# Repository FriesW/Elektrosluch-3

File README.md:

# Elektrosluch-3-Mini
A very small edition of the [Elektrosluch-3](https://github.com/LOM-instruments/Elektrosluch-3) by [LOM Instruments](https://lom.audio/).

## What it is
The Elektrosluch is an open-source device for listening to electromagnetic fields. Two inductors or coils of wire act as antennas to couple with stray magnetic fields. This particular model also functions as a general purpose audio amplifier. All functions are in stereo. Line output and external input are 3.5 mm (1/8") stereo jacks. The device is powered from a 9V battery.

Jonas Gruska of LOM Instruments, the original creator, has made an album using a device with the same circuit. It can be [listened to on Bandcamp](http://zvukolom.bandcamp.com/album/sensing-electromagnetics) and is representative of what you can hear with this device.

## Reason for Creation
1. I find it a fun game to make PCBs as small as possible.
2. The original project lacked a BOM.
3. The original project was made in Eagle. I prefer KiCad.
4. I wanted to use the Elektrosluch as a gift for my brother.

## BOM and Part Selection
Audio capacitors and potentiometer were selected as recommended from the original LOM project. These are the bulkiest portion, and a future development could be replacing these with much smaller equivalences. Everything else was selected to be surface mount and as small as possible. Custom KiCad footprints had to be made for many of the parts. The BOM lists standard inductors for the "antennas," but handwound wire might produce more desirable results, as the inductors will be engineered to reduce coupling as much as possible.

## Assembly
Some projects say "advanced soldering skills required," and you might scoff at it. However, this is not one to scoff at. Small SMD parts are used and spaced very closely together. It is necessary to plan many steps ahead, such that you have enough room to place every component.

## PCBs
The PCB is also [shared through OSH Park](https://oshpark.com/shared_projects/8xzPLFLW) and can be directly ordered from there. You'll get three boards for $8.75. ~However, I might have a few lying around, so if you are going to build one, PM me and I'll look to see if I have extras.~ All gone! Still feel free to PM me if you have any questions.

## Modifications
If you want to further develop the project, [KiCad](http://kicad-pcb.org/) can be obtained for free, as in free speech. The KiCad project files use custom schematic symbols and footprints which are in my [personal KiCad library](https://github.com/FriesW/KiCad-Library).

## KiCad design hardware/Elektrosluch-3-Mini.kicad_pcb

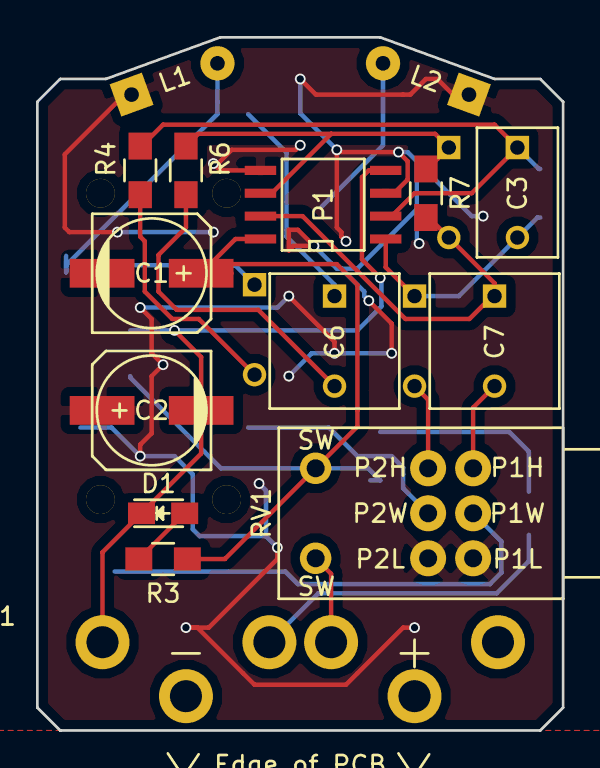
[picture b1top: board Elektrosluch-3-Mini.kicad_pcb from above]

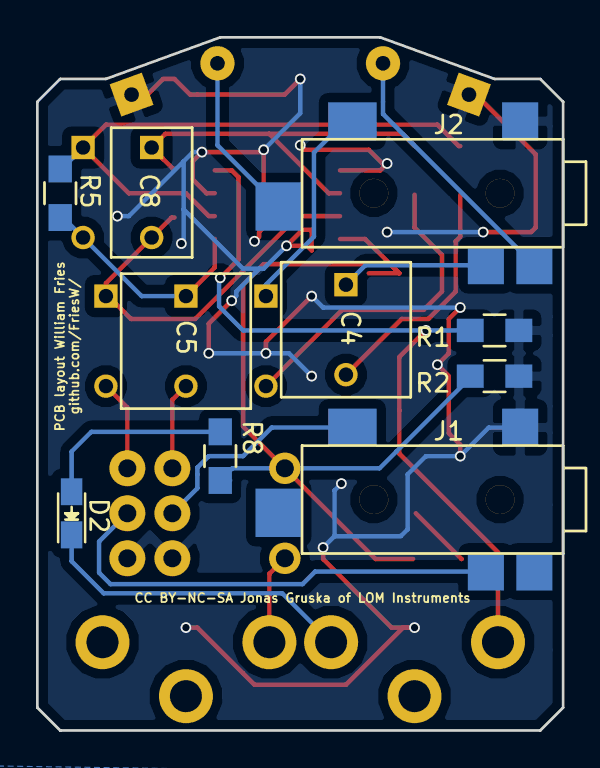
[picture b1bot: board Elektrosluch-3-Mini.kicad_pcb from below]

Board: 2 copper layers, 29.2 x 38.5 mm, 25 parts (10 on the bottom side), 20 nets.

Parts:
BT1: 9V; 9V_Battery_Snaps
C1, C2: 220uF; c_elec_6.3x7.7
C3, C8: 47pF; C_Rect_L7.2_W4.5_P5
C4, C5, C6, C7: 2.2uF; C_Rect_L7.2_W7.2_P5
D1, D2: LED; LED-0805-HandSoldering
J1, J2: JACK_TRS_5PINS; Switchcraft_TRS_Jack_SMD
L1, L2: 22mH; INDUCTOR_V_WO_CIRCLE
P1: DIL8; SOIC-8-N-HandSoldering
R1, R2: 100k; R_0805_HandSoldering
R3, R4, R6, R8: 1k; R_0805_HandSoldering
R5, R7: 390k; R_0805_HandSoldering
RV1: DUAL_SWITCHED_POT; Dual_Switched_Pot

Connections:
+5V: C1.1, P1.8, R1.1, R3.1, R8.1, RV1.7
-5V: BT1.2, C2.2, D1.1, D2.1, P1.4, R2.2
/AO1: C3.2, C5.1, P1.1, R5.2
/AO2: C7.1, C8.2, P1.7, R7.2
/CH1: C3.1, P1.2, R4.2, R5.1
/CH2: C8.1, P1.6, R6.2, R7.1
GND: C1.2, C2.1, J1.1, J2.1, L1.1, L2.1, P1.3, P1.5, R1.2, R2.1, RV1.3, RV1.6
unnamed: BT1.1, RV1.8
unnamed: C4.1, J2.3
unnamed: C4.2, R4.1
unnamed: C5.2, RV1.4
unnamed: C6.1, J2.2
unnamed: C6.2, R6.1
unnamed: C7.2, RV1.1
unnamed: D1.2, R3.2
unnamed: D2.2, R8.2
unnamed: J1.2, RV1.5
unnamed: J1.3, RV1.2
unnamed: J2.4, L2.2
unnamed: J2.5, L1.2

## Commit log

2017-01-17 Added KiCad Library to Readme
2017-01-17 Hardware
    Added KiCad files, removed Eagle files.
2017-01-17 Added Listening Example
2017-01-18 Create BOM.md
    Still need to add Reference Designators.
2017-01-18 Update BOM.md
    Added Reference Designators and LEDs.
2017-01-18 Completed BOM
    Finished LED entry.
2017-01-18 Completed BOM
    This one is actually complete. I forgot to add reference designators for battery clips.
2019-12-15 Fix BOM Links
    Because Mouser broke all my saved URLs...

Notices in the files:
hardware/Elektrosluch-3-Mini.kicad_pcb:
Circuit licensed under CC BY-NC-SA by Jonas Gruska / LOM Instruments
CC BY-NC-SA Jonas Gruska of LOM Instruments
